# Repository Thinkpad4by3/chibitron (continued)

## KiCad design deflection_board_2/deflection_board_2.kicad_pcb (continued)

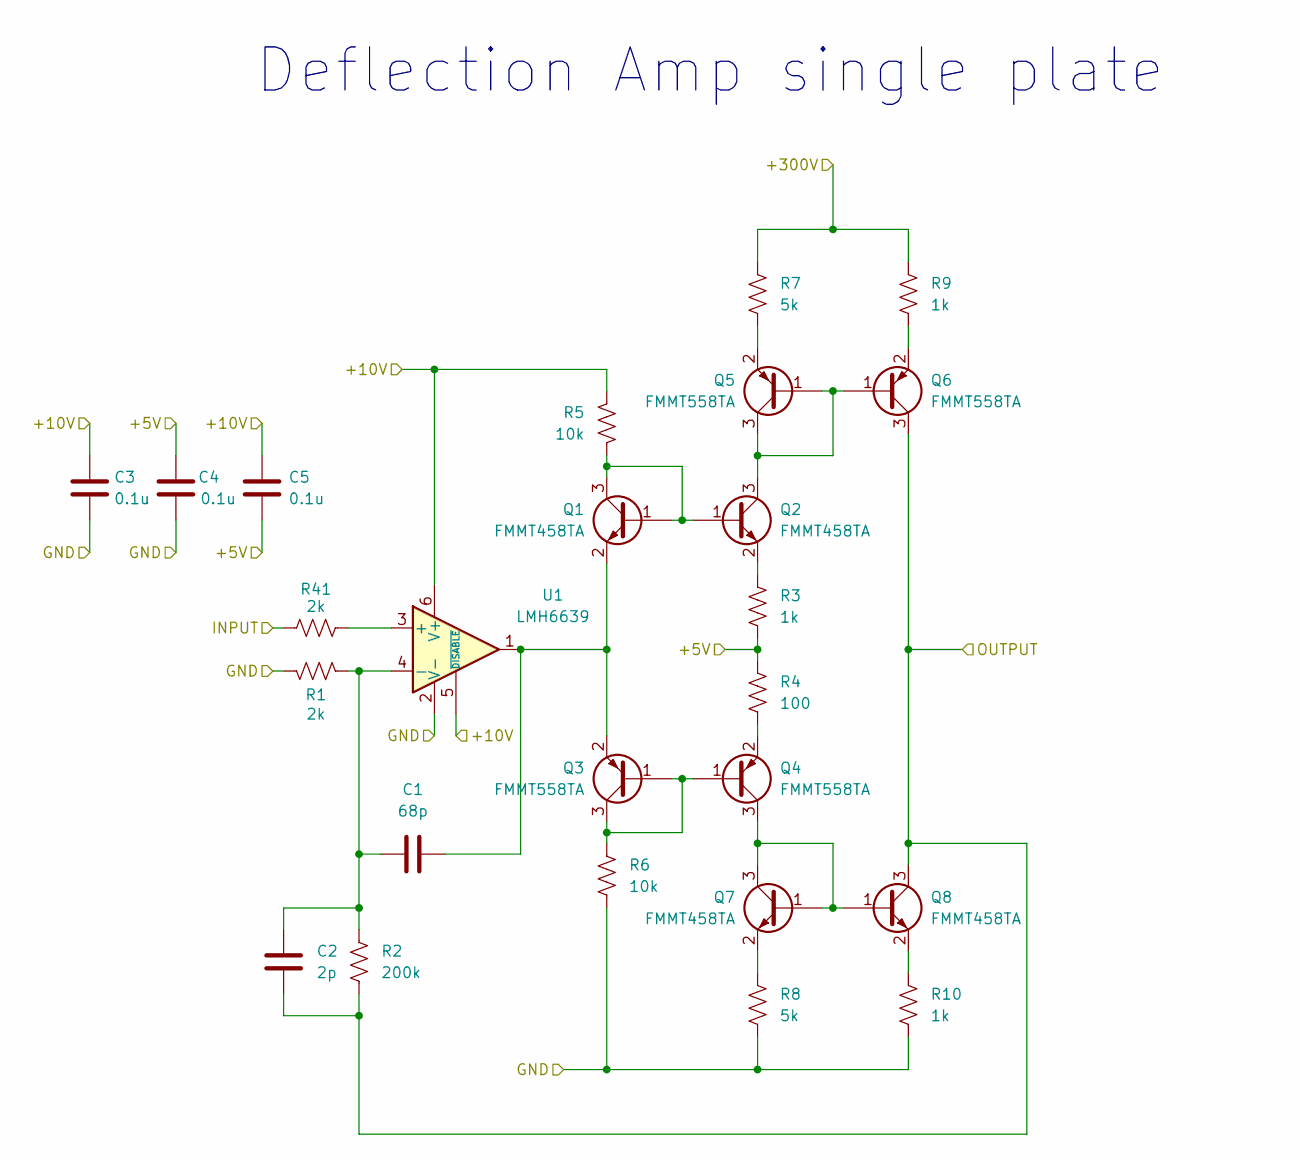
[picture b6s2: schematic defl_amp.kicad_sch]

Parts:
C1: 68p; C_0603_1608Metric_Pad1.08x0.95mm_HandSolder
C2: 2p; C_0603_1608Metric_Pad1.08x0.95mm_HandSolder
C3, C4, C5: 0.1u; C_0603_1608Metric_Pad1.08x0.95mm_HandSolder
Q1, Q2, Q7, Q8: FMMT458TA; SOT-23
Q3, Q4, Q5, Q6: FMMT558TA; SOT-23
R1, R41: 2k; R_1206_3216Metric_Pad1.30x1.75mm_HandSolder
R2: 200k; R_1206_3216Metric_Pad1.30x1.75mm_HandSolder
R3, R9, R10: 1k; R_1206_3216Metric_Pad1.30x1.75mm_HandSolder
R4: 100; R_1206_3216Metric_Pad1.30x1.75mm_HandSolder
R5, R6: 10k; R_0603_1608Metric_Pad0.98x0.95mm_HandSolder
R7, R8: 5k; R_1206_3216Metric_Pad1.30x1.75mm_HandSolder
U1: LMH6639; TSOT-23-6

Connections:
+5V: C4.1, C5.2, R3.2, R4.1; also elsewhere on the board
+10V: C3.1, C5.1, R5.1, U1.5 (~DISABLE), U1.6 (V+); also elsewhere on the board
+300V: R7.1, R9.1; also elsewhere on the board
/Deflection Amp X1/INPUT: R41.1; also elsewhere on the board
/Deflection Amp X1/OUTPUT: C2.1, Q6.3 (C), Q8.3 (C), R2.2; also elsewhere on the board
GND: C3.2, C4.2, R1.1, R6.2, R8.2, R10.2, U1.2 (V-); also elsewhere on the board
unnamed: Q1.1 (B), Q1.3 (C), Q2.1 (B), R5.2
unnamed: C1.2, Q1.2 (E), Q3.2 (E), U1.1
unnamed: Q2.3 (C), Q5.1 (B), Q5.3 (C), Q6.1 (B)
unnamed: Q2.2 (E), R3.1
unnamed: Q3.1 (B), Q3.3 (C), Q4.1 (B), R6.1
unnamed: Q4.3 (C), Q7.1 (B), Q7.3 (C), Q8.1 (B)
unnamed: Q4.2 (E), R4.2
unnamed: Q5.2 (E), R7.2
unnamed: Q6.2 (E), R9.2
unnamed: Q7.2 (E), R8.1
unnamed: Q8.2 (E), R10.1
unnamed: R41.2, U1.3 (+)
unnamed: C1.1, C2.2, R1.2, R2.1, U1.4 (-)

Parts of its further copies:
C6, C7, C8, C11, C12, C13, C16, C17, C18: 0.1u; C_0603_1608Metric_Pad1.08x0.95mm_HandSolder
C9, C14, C19: 2p; C_0603_1608Metric_Pad1.08x0.95mm_HandSolder
C10, C15, C20: 68p; C_0603_1608Metric_Pad1.08x0.95mm_HandSolder
Q9, Q11, Q14, Q16, Q17, Q19, Q22, Q24, Q25, Q27, Q30, Q32: FMMT458TA; SOT-23
Q10, Q12, Q13, Q15, Q18, Q20, Q21, Q23, Q26, Q28, Q29, Q31: FMMT558TA; SOT-23
R11, R21, R31, R42, R43, R44: 2k; R_1206_3216Metric_Pad1.30x1.75mm_HandSolder
R12, R22, R32: 200k; R_1206_3216Metric_Pad1.30x1.75mm_HandSolder
R13, R14, R23, R24, R33, R34: 10k; R_0603_1608Metric_Pad0.98x0.95mm_HandSolder
R15, R18, R25, R28, R35, R38: 5k; R_1206_3216Metric_Pad1.30x1.75mm_HandSolder
R16, R19, R20, R26, R29, R30, R36, R39, R40: 1k; R_1206_3216Metric_Pad1.30x1.75mm_HandSolder
R17, R27, R37: 100; R_1206_3216Metric_Pad1.30x1.75mm_HandSolder
U2, U3, U4: LMH6639; TSOT-23-6

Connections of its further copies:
+5V: C7.1, C8.2, C12.1, C13.2, C17.1, C18.2, R16.2, R17.1, R26.2, R27.1, R36.2, R37.1; also elsewhere on the board
+10V: C6.1, C8.1, C11.1, C13.1, C16.1, C18.1, R13.1, R23.1, R33.1, U2.5 (~DISABLE), U2.6 (V+), U3.5 (~DISABLE), U3.6 (V+), U4.5 (~DISABLE), U4.6 (V+); also elsewhere on the board
+300V: R15.1, R19.1, R25.1, R29.1, R35.1, R39.1; also elsewhere on the board
/Deflection Amp X2/INPUT: R42.1; also elsewhere on the board
/Deflection Amp X2/OUTPUT: C9.1, Q15.3 (C), Q16.3 (C), R12.2; also elsewhere on the board
/Deflection Amp Y1/INPUT: R43.1; also elsewhere on the board
/Deflection Amp Y1/OUTPUT: C14.1, Q23.3 (C), Q24.3 (C), R22.2; also elsewhere on the board
/Deflection Amp Y2/INPUT: R44.1; also elsewhere on the board
/Deflection Amp Y2/OUTPUT: C19.1, Q31.3 (C), Q32.3 (C), R32.2; also elsewhere on the board
GND: C6.2, C7.2, C11.2, C12.2, C16.2, C17.2, R11.1, R14.2, R18.2, R20.2, R21.1, R24.2, R28.2, R30.2, R31.1, R34.2, R38.2, R40.2, U2.2 (V-), U3.2 (V-), U4.2 (V-); also elsewhere on the board
unnamed: Q10.1 (B), Q10.3 (C), Q12.1 (B), R14.1
unnamed: C10.2, Q9.2 (E), Q10.2 (E), U2.1
unnamed: Q9.1 (B), Q9.3 (C), Q11.1 (B), R13.2
unnamed: Q11.3 (C), Q13.1 (B), Q13.3 (C), Q15.1 (B)
unnamed: Q11.2 (E), R16.1
unnamed: Q12.3 (C), Q14.1 (B), Q14.3 (C), Q16.1 (B)
unnamed: Q12.2 (E), R17.2
unnamed: Q13.2 (E), R15.2
unnamed: Q14.2 (E), R18.1
unnamed: Q15.2 (E), R19.2
unnamed: Q16.2 (E), R20.1
unnamed: Q17.1 (B), Q17.3 (C), Q19.1 (B), R23.2
unnamed: C15.2, Q17.2 (E), Q18.2 (E), U3.1
unnamed: Q18.1 (B), Q18.3 (C), Q20.1 (B), R24.1
unnamed: Q19.3 (C), Q21.1 (B), Q21.3 (C), Q23.1 (B)
unnamed: Q19.2 (E), R26.1
unnamed: Q20.3 (C), Q22.1 (B), Q22.3 (C), Q24.1 (B)
unnamed: Q20.2 (E), R27.2
unnamed: Q21.2 (E), R25.2
unnamed: Q22.2 (E), R28.1
unnamed: Q23.2 (E), R29.2
unnamed: Q24.2 (E), R30.1
unnamed: Q25.1 (B), Q25.3 (C), Q27.1 (B), R33.2
unnamed: C20.2, Q25.2 (E), Q26.2 (E), U4.1
unnamed: Q26.1 (B), Q26.3 (C), Q28.1 (B), R34.1
unnamed: Q27.3 (C), Q29.1 (B), Q29.3 (C), Q31.1 (B)
unnamed: Q27.2 (E), R36.1
unnamed: Q28.3 (C), Q30.1 (B), Q30.3 (C), Q32.1 (B)
unnamed: Q28.2 (E), R37.2
unnamed: Q29.2 (E), R35.2
unnamed: Q30.2 (E), R38.1
unnamed: Q31.2 (E), R39.2
unnamed: Q32.2 (E), R40.1
unnamed: R42.2, U2.3 (+)
unnamed: C9.2, C10.1, R11.2, R12.1, U2.4 (-)
unnamed: R43.2, U3.3 (+)
unnamed: C14.2, C15.1, R21.2, R22.1, U3.4 (-)
unnamed: R44.2, U4.3 (+)
unnamed: C19.2, C20.1, R31.2, R32.1, U4.4 (-)

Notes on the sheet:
Deflection Amp single plate

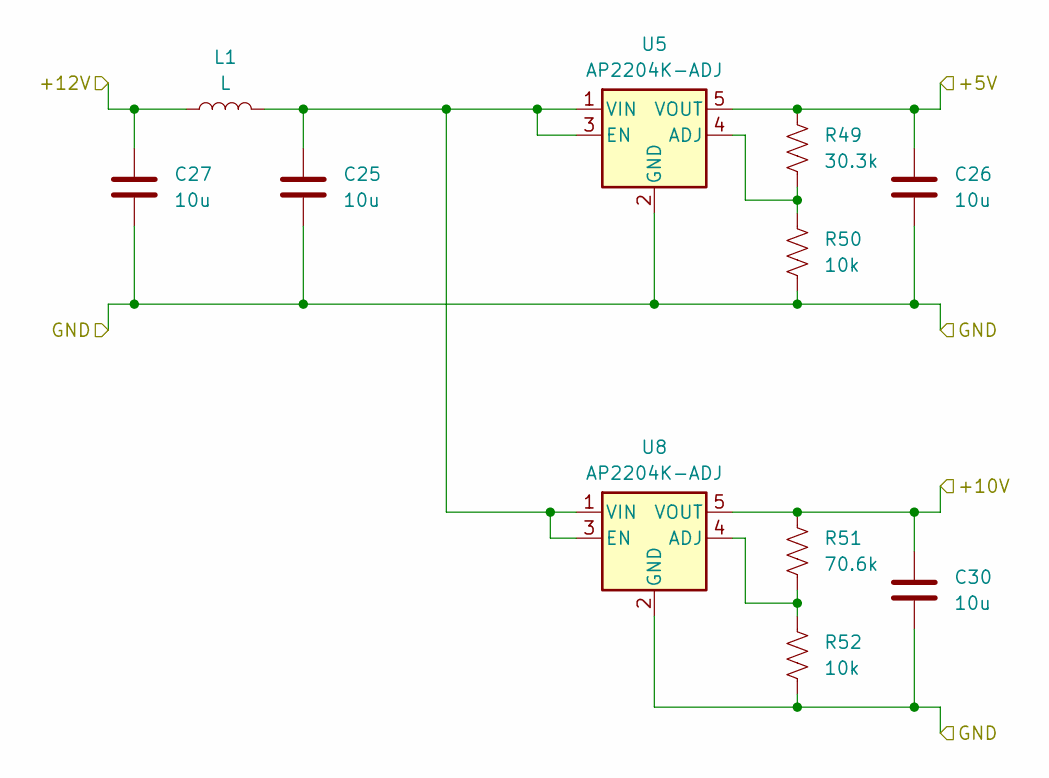
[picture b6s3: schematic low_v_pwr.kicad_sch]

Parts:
C25, C26, C27, C30: 10u; C_0603_1608Metric
L1: L; L_APV_ANR4018
R49: 30.3k; R_0805_2012Metric
R50, R52: 10k; R_0805_2012Metric
R51: 70.6k; R_0805_2012Metric
U5, U8: AP2204K-ADJ; SOT-23-5

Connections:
+5V: C26.1, R49.1, U5.5 (VOUT); also elsewhere on the board
+10V: C30.1, R51.1, U8.5 (VOUT); also elsewhere on the board
+12V: C27.1, L1.1; also elsewhere on the board
GND: C25.2, C26.2, C27.2, C30.2, R50.2, R52.2, U5.2 (GND), U8.2 (GND); also elsewhere on the board
unnamed: R49.2, R50.1, U5.4 (ADJ)
unnamed: C25.1, L1.2, U5.1 (VIN), U5.3 (EN), U8.1 (VIN), U8.3 (EN)
unnamed: R51.2, R52.1, U8.4 (ADJ)

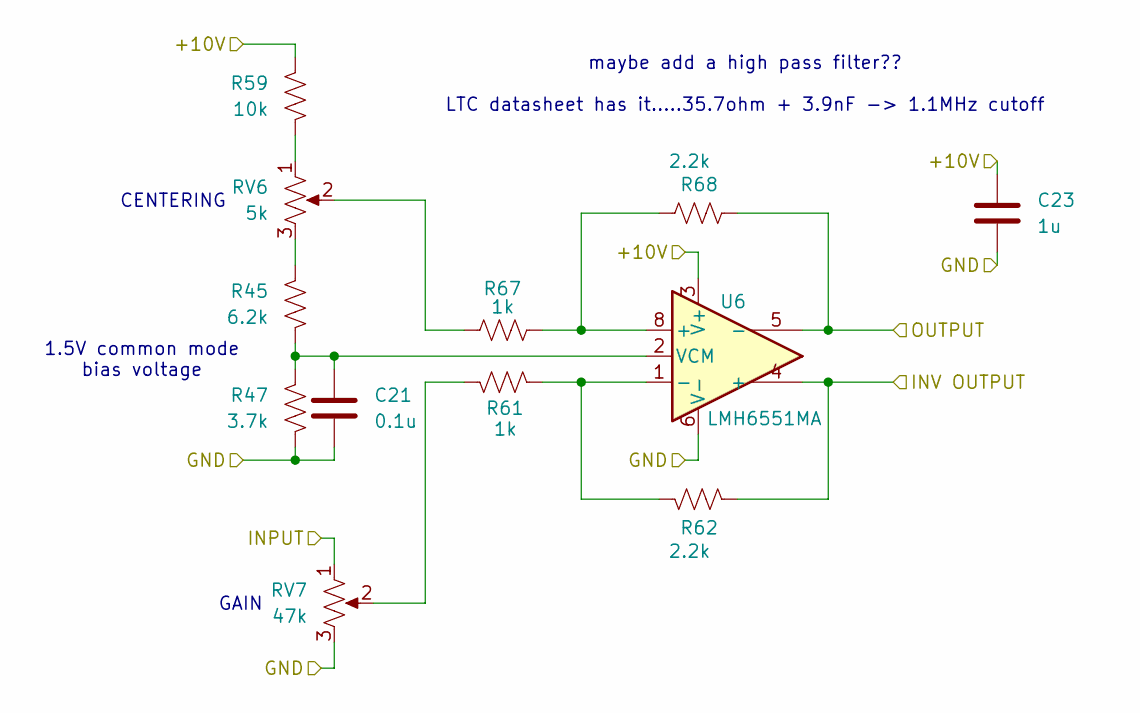
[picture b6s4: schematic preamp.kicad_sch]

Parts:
C21: 0.1u; C_0603_1608Metric
C23: 1u; C_0603_1608Metric
R45: 6.2k; R_0603_1608Metric
R47: 3.7k; R_0603_1608Metric
R59: 10k; R_0603_1608Metric_Pad0.98x0.95mm_HandSolder
R61, R67: 1k; R_0603_1608Metric_Pad0.98x0.95mm_HandSolder
R62, R68: 2.2k; R_0603_1608Metric_Pad0.98x0.95mm_HandSolder
RV6: 5k; Potentiometer_Bourns_3296W_Vertical
RV7: 47k; Potentiometer_Bourns_3296W_Vertical
U6: LMH6551MA; SOIC-8_3.9x4.9mm_P1.27mm

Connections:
+10V: C23.1, R59.1, U6.3 (V+); also elsewhere on the board
/X Pre-amp/INPUT: RV7.1; also elsewhere on the board
/X Pre-amp/INV OUTPUT: R62.2, U6.4 (+); also elsewhere on the board
/X Pre-amp/OUTPUT: R68.2, U6.5 (-); also elsewhere on the board
GND: C21.2, C23.2, R47.2, RV7.3, U6.6 (V-); also elsewhere on the board
unnamed: R45.1, RV6.3
unnamed: R59.2, RV6.1
unnamed: R61.1, R62.1, U6.1 (-)
unnamed: R61.2, RV7.2
unnamed: R67.1, R68.1, U6.8 (+)
unnamed: R67.2, RV6.2
unnamed: C21.1, R45.2, R47.1, U6.2 (VCM)

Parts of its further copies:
C22: 0.1u; C_0603_1608Metric
C24: 1u; C_0603_1608Metric
R63: 10k; R_0603_1608Metric_Pad0.98x0.95mm_HandSolder
R65, R69: 1k; R_0603_1608Metric_Pad0.98x0.95mm_HandSolder
R66, R70: 2.2k; R_0603_1608Metric_Pad0.98x0.95mm_HandSolder
RV8: 5k; Potentiometer_Bourns_3296W_Vertical
RV9: 47k; Potentiometer_Bourns_3296W_Vertical
U7: LMH6551MA; SOIC-8_3.9x4.9mm_P1.27mm

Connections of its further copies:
+10V: C24.1, R63.1, U7.3 (V+); also elsewhere on the board
/Y Pre-amp/INPUT: RV9.1; also elsewhere on the board
/Y Pre-amp/INV OUTPUT: R66.2, U7.4 (+); also elsewhere on the board
/Y Pre-amp/OUTPUT: R70.2, U7.5 (-); also elsewhere on the board
GND: C22.2, C24.2, RV9.3, U7.6 (V-); also elsewhere on the board
unnamed 64: RV8.3; also elsewhere on the board
unnamed: R63.2, RV8.1
unnamed: R65.1, R66.1, U7.1 (-)
unnamed: R65.2, RV9.2
unnamed: R69.1, R70.1, U7.8 (+)
unnamed: R69.2, RV8.2
unnamed 86: C22.1, U7.2 (VCM); also elsewhere on the board

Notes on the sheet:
CENTERING
maybe add a high pass filter?? LTC datasheet has it.....35.7ohm + 3.9nF -> 1.1MHz cutoff
GAIN
1.5V common mode bias voltage

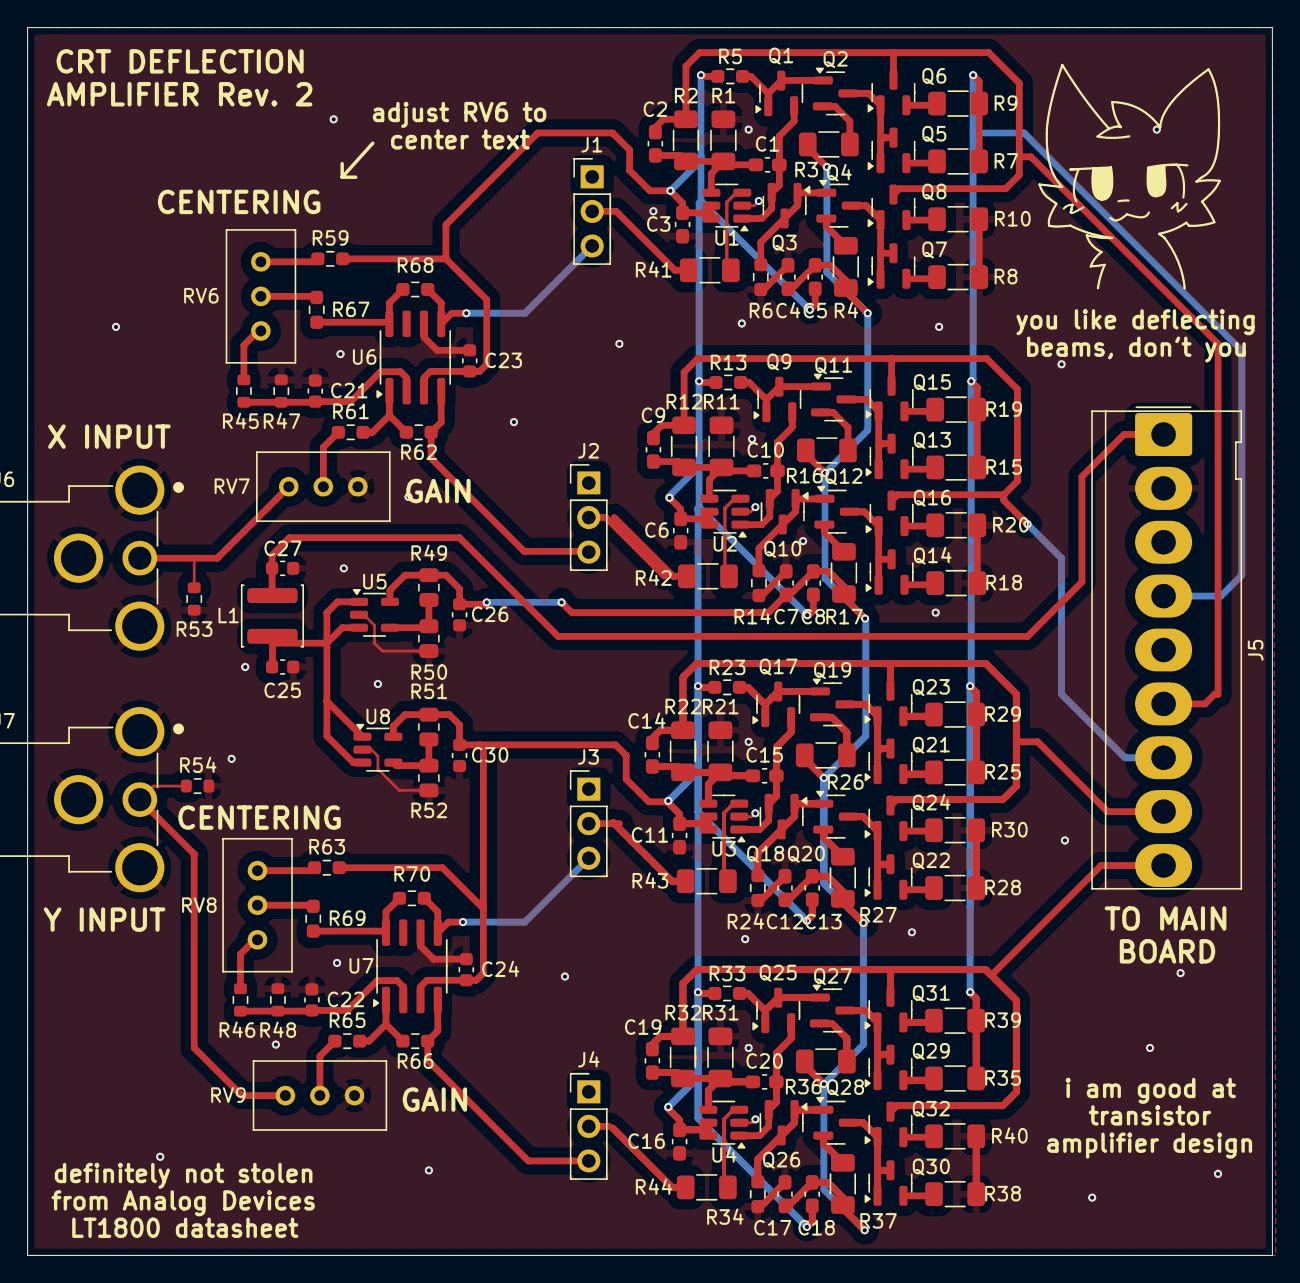
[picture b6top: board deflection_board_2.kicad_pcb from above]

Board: 2 copper layers, 91.5 x 90.2 mm, 144 parts (0 on the bottom side), 88 nets.

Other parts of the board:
R46: 6.25k; R_0603_1608Metric
R48: 3.75k; R_0603_1608Metric

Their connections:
GND: R48.2; also elsewhere on the board
unnamed 64: R46.1; also elsewhere on the board
unnamed 86: R46.2, R48.1; also elsewhere on the board

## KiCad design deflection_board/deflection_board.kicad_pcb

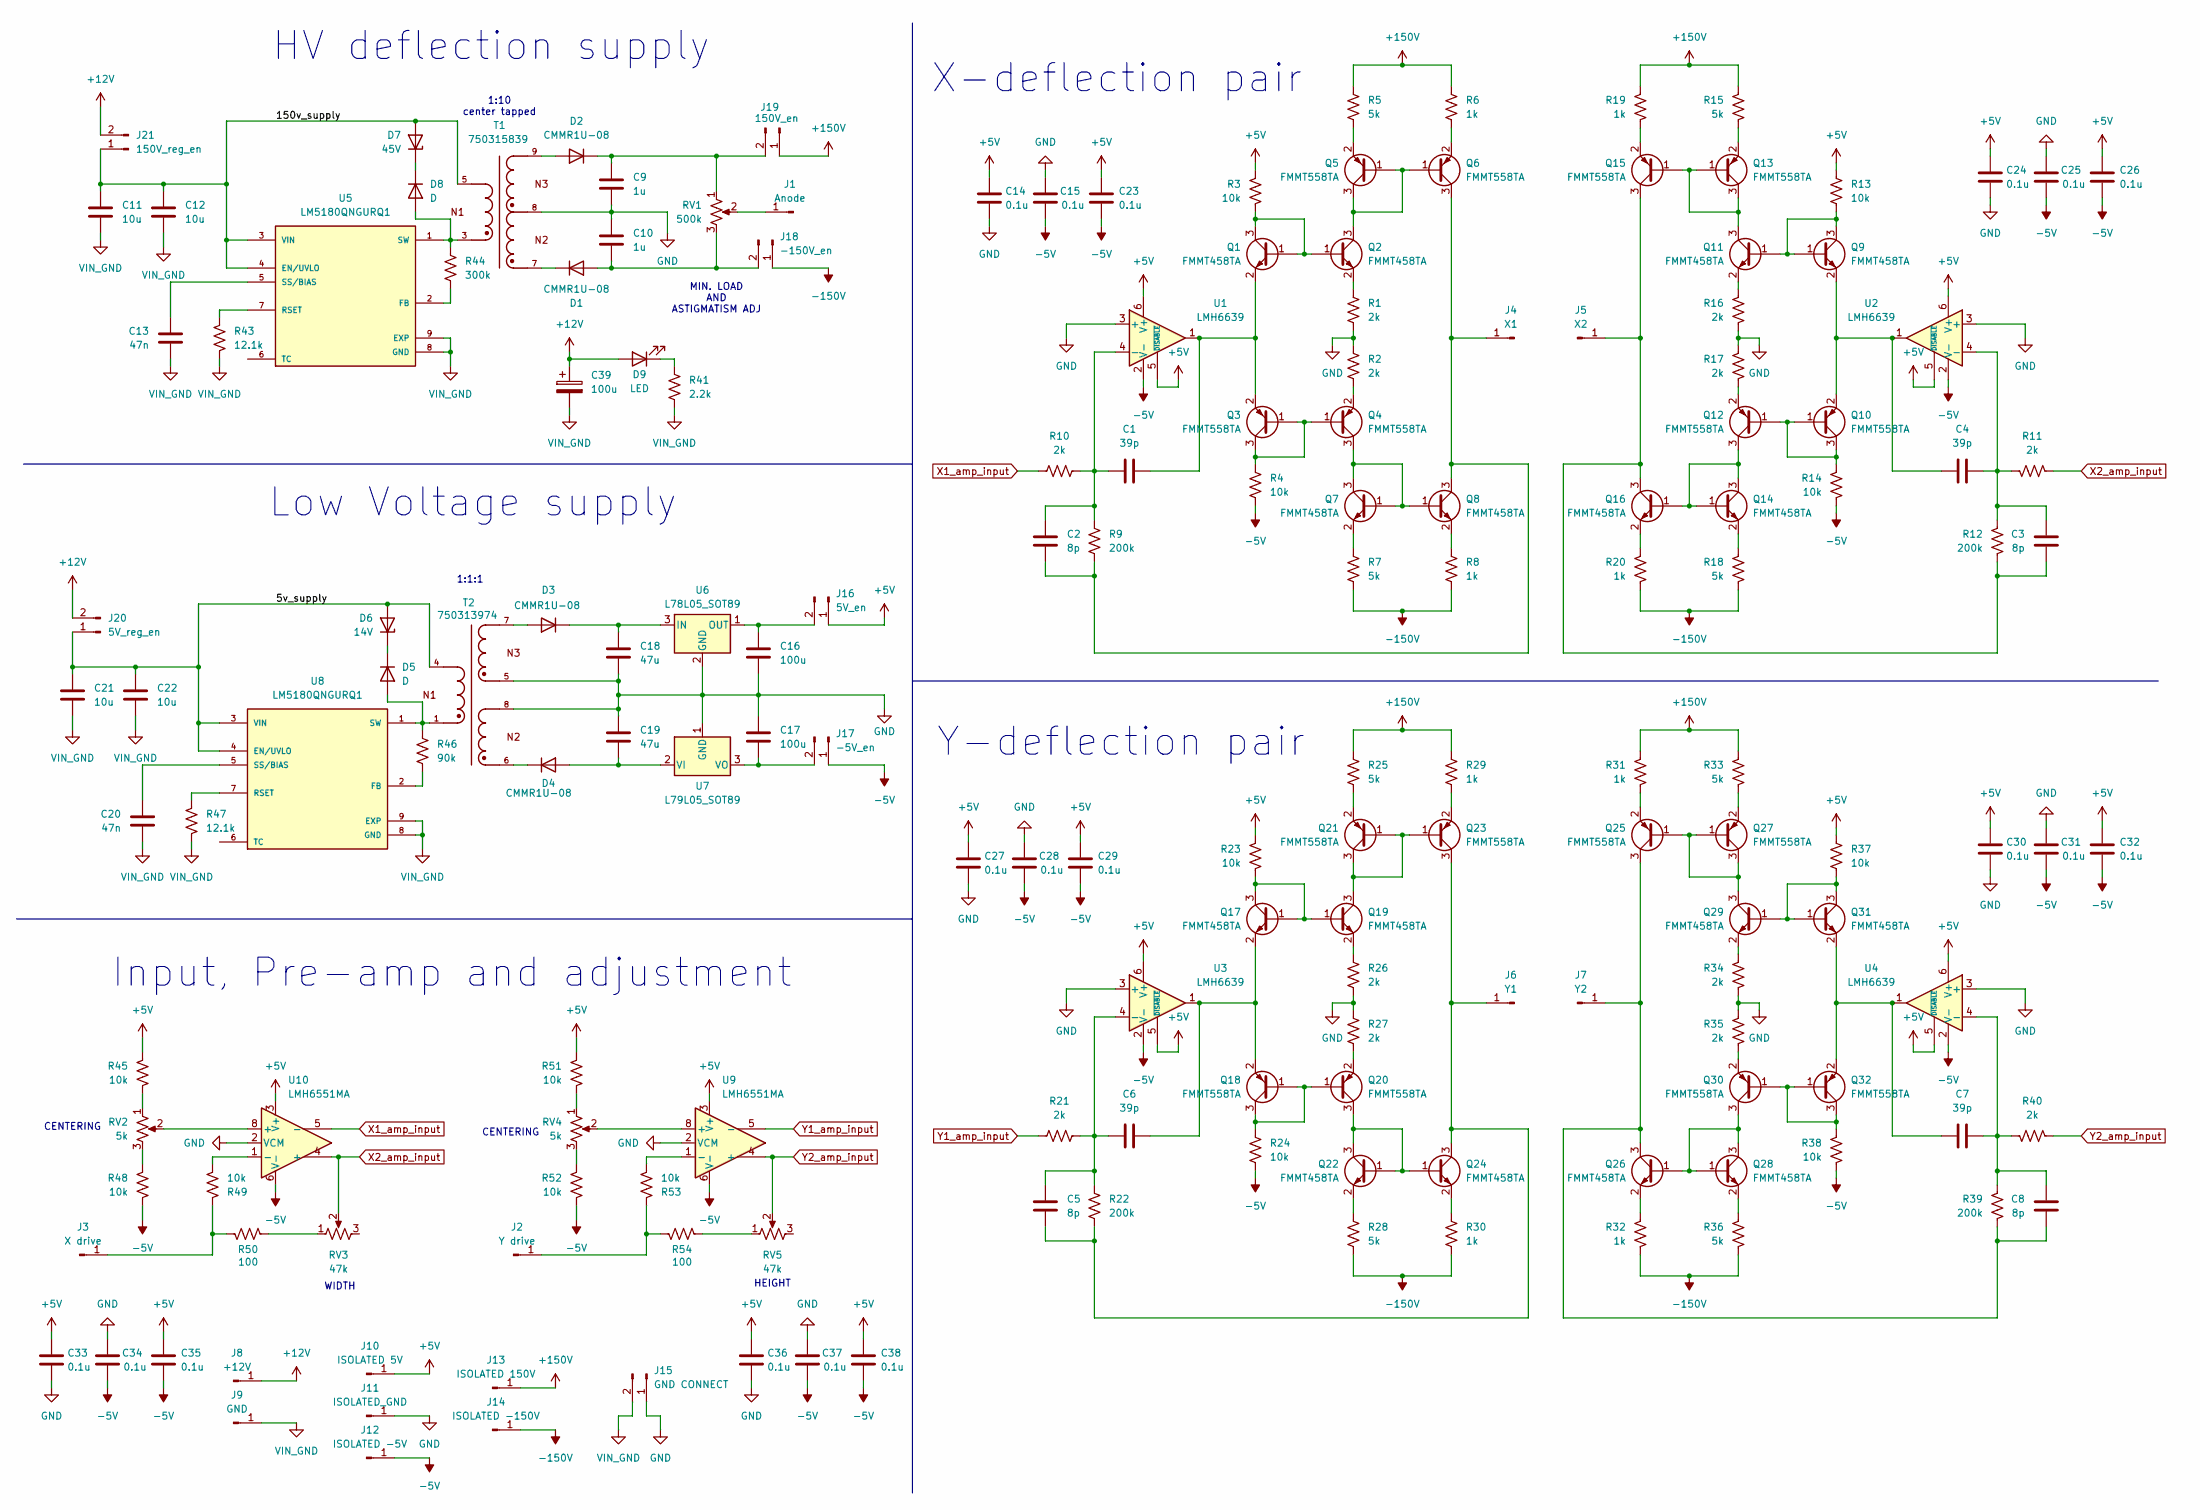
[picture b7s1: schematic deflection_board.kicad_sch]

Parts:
C1, C4, C6, C7: 39p; C_0603_1608Metric_Pad1.08x0.95mm_HandSolder
C2, C3, C5, C8: 8p; C_0603_1608Metric_Pad1.08x0.95mm_HandSolder
C9, C10: 1u; C_1812_4532Metric_Pad1.57x3.40mm_HandSolder
C11, C12, C21, C22: 10u; C_0805_2012Metric_Pad1.18x1.45mm_HandSolder
C13, C20: 47n; C_0603_1608Metric_Pad1.08x0.95mm_HandSolder
C14, C15, C23, C24, C25, C26, C27, C28, C29, C30, C31, C32, C33, C34, C35, C36, C37, C38: 0.1u; C_0603_1608Metric_Pad1.08x0.95mm_HandSolder
C16, C17: 100u; C_1206_3216Metric_Pad1.33x1.80mm_HandSolder
C18, C19: 47u; C_1210_3225Metric_Pad1.33x2.70mm_HandSolder
C39: 100u; C_Elec_6.3x7.7
D1, D2, D3, D4: CMMR1U-08; D_SOD-123F
D5, D8: D; D_SOD-123
D6: 14V; D_SOD-123
D7: 45V; D_SOD-123
D9: LED; LED_0805_2012Metric
J1: Anode; PinHeader_1x01_P2.54mm_Vertical
J2: Y drive; PinHeader_1x01_P2.54mm_Vertical
J3: X drive; PinHeader_1x01_P2.54mm_Vertical
J4: X1; PinHeader_1x01_P2.54mm_Vertical
J5: X2; PinHeader_1x01_P2.54mm_Vertical
J6: Y1; PinHeader_1x01_P2.54mm_Vertical
J7: Y2; PinHeader_1x01_P2.54mm_Vertical
J8: +12V; PinHeader_1x01_P2.54mm_Vertical
J9: GND; PinHeader_1x01_P2.54mm_Vertical
J10: ISOLATED 5V; PinHeader_1x01_P2.54mm_Vertical
J11: ISOLATED_GND; PinHeader_1x01_P2.54mm_Vertical
J12: ISOLATED -5V; PinHeader_1x01_P2.54mm_Vertical
J13: ISOLATED 150V; PinHeader_1x01_P2.54mm_Vertical
J14: ISOLATED -150V; PinHeader_1x01_P2.54mm_Vertical
J15: GND CONNECT; PinHeader_1x02_P2.54mm_Vertical
J16: 5V_en; PinHeader_1x02_P2.54mm_Vertical
J17: -5V_en; PinHeader_1x02_P2.54mm_Vertical
J18: -150V_en; PinHeader_1x02_P2.54mm_Vertical
J19: 150V_en; PinHeader_1x02_P2.54mm_Vertical
J20: 5V_reg_en; PinHeader_1x02_P2.54mm_Vertical
J21: 150V_reg_en; PinHeader_1x02_P2.54mm_Vertical
Q1, Q2, Q7, Q8, Q9, Q11, Q14, Q16, Q17, Q19, Q22, Q24, Q26, Q28, Q29, Q31: FMMT458TA; SOT-23
Q3, Q4, Q5, Q6, Q10, Q12, Q13, Q15, Q18, Q20, Q21, Q23, Q25, Q27, Q30, Q32: FMMT558TA; SOT-23
R1, R2, R10, R11, R16, R17, R21, R26, R27, R34, R35, R40: 2k; R_1206_3216Metric_Pad1.30x1.75mm_HandSolder
R3, R4, R13, R14, R23, R24, R37, R38, R45, R48, R49, R51, R52, R53: 10k; R_0603_1608Metric_Pad0.98x0.95mm_HandSolder
R5, R7, R15, R18, R25, R28, R33, R36: 5k; R_1206_3216Metric_Pad1.30x1.75mm_HandSolder
R6, R8, R19, R20, R29, R30, R31, R32: 1k; R_1206_3216Metric_Pad1.30x1.75mm_HandSolder
R9, R12, R22, R39: 200k; R_1206_3216Metric_Pad1.30x1.75mm_HandSolder
R41: 2.2k; R_0805_2012Metric_Pad1.20x1.40mm_HandSolder
R43, R47: 12.1k; R_0603_1608Metric_Pad0.98x0.95mm_HandSolder
R44: 300k; R_0603_1608Metric_Pad0.98x0.95mm_HandSolder
R46: 90k; R_0603_1608Metric_Pad0.98x0.95mm_HandSolder
R50, R54: 100; R_0603_1608Metric_Pad0.98x0.95mm_HandSolder
RV1: 500k; Potentiometer_Bourns_3296W_Vertical
RV2, RV4: 5k; Potentiometer_Bourns_3296W_Vertical
RV3, RV5: 47k; Potentiometer_Bourns_3296W_Vertical
T1: 750315839; WE-FLYLT_EP13_5465; PART-NUMBER 750315839
T2: 750313974; WE-FLYLT_EP10_6052; PART-NUMBER 750313974
U1, U2, U3, U4: LMH6639; TSOT-23-6
U5, U8: LM5180QNGURQ1; SON80P400X400X80-9N; PARTREV A
U6: L78L05_SOT89; SOT-89-3
U7: L79L05_SOT89; SOT-89-3
U9, U10: LMH6551MA; SOIC-8_3.9x4.9mm_P1.27mm

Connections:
+5V: C14.1, C23.1, C24.1, C26.1, C27.1, C29.1, C30.1, C32.1, C33.1, C35.1, C36.1, C38.1, J10.1, J16.1, R3.1, R13.1, R23.1, R37.1, R45.1, R51.1, U1.5 (~DISABLE), U1.6 (V+), U2.5 (~DISABLE), U2.6 (V+), U3.5 (~DISABLE), U3.6 (V+), U4.5 (~DISABLE), U4.6 (V+), U9.3 (V+), U10.3 (V+)
+12V: C39.1, D9.2 (A), J8.1, J20.2, J21.2
+150V: J13.1, J19.1, R5.1, R6.1, R15.1, R19.1, R25.1, R29.1, R31.1, R33.1
-5V: C15.2, C23.2, C25.2, C26.2, C28.2, C29.2, C31.2, C32.2, C34.2, C35.2, C37.2, C38.2, J12.1, J17.1, R4.2, R14.2, R24.2, R38.2, R48.2, R52.2, U1.2 (V-), U2.2 (V-), U3.2 (V-), U4.2 (V-), U9.6 (V-), U10.6 (V-)
-150V: J14.1, J18.1, R7.2, R8.2, R18.2, R20.2, R28.2, R30.2, R32.2, R36.2
/5v_supply: C21.1, C22.1, D6.2 (A), J20.1, T2.4, U8.3 (VIN), U8.4 (EN/UVLO)
/150v_supply: C11.1, C12.1, D7.2 (A), J21.1, T1.5, U5.3 (VIN), U5.4 (EN/UVLO)
GND: C9.2, C10.1, C14.2, C15.1, C16.2, C17.1, C18.2, C19.1, C24.2, C25.1, C27.2, C28.1, C30.2, C31.1, C33.2, C34.1, C36.2, C37.1, J11.1, J15.1, R1.2, R2.1, R16.2, R17.1, R26.2, R27.1, R34.2, R35.1, T1.8, T2.5, T2.8, U1.3 (+), U2.3 (+), U3.3 (+), U4.3 (+), U6.2 (GND), U7.1 (GND), U9.2 (VCM), U10.2 (VCM)
unnamed: C10.2, D1.2 (A), J18.2, RV1.3
unnamed: D1.1 (K), T1.7
unnamed: D2.2 (A), T1.9
unnamed: C9.1, D2.1 (K), J19.2, RV1.1
unnamed: D3.2 (A), T2.7
unnamed: C18.1, D3.1 (K), U6.3 (IN)
unnamed: C19.2, D4.2 (A), U7.2 (VI)
unnamed: D4.1 (K), T2.6
unnamed: D5.2 (A), R46.1, T2.1, U8.1 (SW)
unnamed: D5.1 (K), D6.1 (K)
unnamed: D7.1 (K), D8.1 (K)
unnamed: D8.2 (A), R44.1, T1.3, U5.1 (SW)
unnamed: D9.1 (K), R41.2
unnamed: J1.1, RV1.2
unnamed: J2.1, R53.1, R54.1
unnamed: J3.1, R49.1, R50.1
unnamed: C2.1, J4.1, Q6.3 (C), Q8.3 (C), R9.2
unnamed: C3.1, J5.1, Q15.3 (C), Q16.3 (C), R12.2
unnamed: C5.1, J6.1, Q23.3 (C), Q24.3 (C), R22.2
unnamed: C8.1, J7.1, Q25.3 (C), Q26.3 (C), R39.2
unnamed: C16.1, J16.2, U6.1 (OUT)
unnamed: C17.2, J17.2, U7.3 (VO)
unnamed: Q1.1 (B), Q1.3 (C), Q2.1 (B), R3.2
unnamed: C1.2, Q1.2 (E), Q3.2 (E), U1.1
unnamed: Q2.3 (C), Q5.1 (B), Q5.3 (C), Q6.1 (B)
unnamed: Q2.2 (E), R1.1
unnamed: Q3.1 (B), Q3.3 (C), Q4.1 (B), R4.1
unnamed: Q4.3 (C), Q7.1 (B), Q7.3 (C), Q8.1 (B)
unnamed: Q4.2 (E), R2.2
unnamed: Q5.2 (E), R5.2
unnamed: Q6.2 (E), R6.2
unnamed: Q7.2 (E), R7.1
unnamed: Q8.2 (E), R8.1
unnamed: Q10.1 (B), Q10.3 (C), Q12.1 (B), R14.1
unnamed: C4.2, Q9.2 (E), Q10.2 (E), U2.1
unnamed: Q9.1 (B), Q9.3 (C), Q11.1 (B), R13.2
unnamed: Q11.3 (C), Q13.1 (B), Q13.3 (C), Q15.1 (B)
unnamed: Q11.2 (E), R16.1
unnamed: Q12.3 (C), Q14.1 (B), Q14.3 (C), Q16.1 (B)
unnamed: Q12.2 (E), R17.2
unnamed: Q13.2 (E), R15.2
unnamed: Q14.2 (E), R18.1
unnamed: Q15.2 (E), R19.2
unnamed: Q16.2 (E), R20.1
unnamed: Q17.1 (B), Q17.3 (C), Q19.1 (B), R23.2
unnamed: C6.2, Q17.2 (E), Q18.2 (E), U3.1
unnamed: Q18.1 (B), Q18.3 (C), Q20.1 (B), R24.1
unnamed: Q19.3 (C), Q21.1 (B), Q21.3 (C), Q23.1 (B)
unnamed: Q19.2 (E), R26.1
unnamed: Q20.3 (C), Q22.1 (B), Q22.3 (C), Q24.1 (B)
unnamed: Q20.2 (E), R27.2
unnamed: Q21.2 (E), R25.2
unnamed: Q22.2 (E), R28.1
unnamed: Q23.2 (E), R29.2
unnamed: Q24.2 (E), R30.1
unnamed: Q25.1 (B), Q27.1 (B), Q27.3 (C), Q29.3 (C)
unnamed: Q25.2 (E), R31.2
unnamed: Q26.1 (B), Q28.1 (B), Q28.3 (C), Q30.3 (C)
unnamed: Q26.2 (E), R32.1
unnamed: Q27.2 (E), R33.2
unnamed: Q28.2 (E), R36.1
unnamed: Q29.1 (B), Q31.1 (B), Q31.3 (C), R37.2
unnamed: Q29.2 (E), R34.1
unnamed: Q30.1 (B), Q32.1 (B), Q32.3 (C), R38.1
unnamed: Q30.2 (E), R35.2
unnamed: C7.2, Q31.2 (E), Q32.2 (E), U4.1
unnamed: R45.2, RV2.1
unnamed: R48.1, RV2.3
unnamed: R49.2, U10.1 (-)
unnamed: R50.2, RV3.1
unnamed: R51.2, RV4.1
unnamed: R52.1, RV4.3
unnamed: R53.2, U9.1 (-)
unnamed: R54.2, RV5.1
unnamed: RV2.2, U10.8 (+)
unnamed: RV4.2, U9.8 (+)
unnamed: C1.1, C2.2, R9.1, R10.2, U1.4 (-)
unnamed: C3.2, C4.1, R11.2, R12.1, U2.4 (-)
unnamed: C5.2, C6.1, R21.2, R22.1, U3.4 (-)
unnamed: C7.1, C8.2, R39.1, R40.2, U4.4 (-)
unnamed: R44.2, U5.2 (FB)
unnamed: R43.1, U5.7 (RSET)
unnamed: C13.1, U5.5 (SS/BIAS)
unnamed: R46.2, U8.2 (FB)
unnamed: R47.1, U8.7 (RSET)
unnamed: C20.1, U8.5 (SS/BIAS)
VIN_GND: C11.2, C12.2, C13.2, C20.2, C21.2, C22.2, C39.2, J9.1, J15.2, R41.1, R43.2, R47.2, U5.8 (GND), U5.9 (EXP), U8.8 (GND), U8.9 (EXP)
X1_amp_input: R10.1, U10.5 (-)
X2_amp_input: R11.1, RV3.2, U10.4 (+)
Y1_amp_input: R21.1, U9.5 (-)
Y2_amp_input: R40.1, RV5.2, U9.4 (+)

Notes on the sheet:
Low Voltage supply
MIN. LOAD AND ASTIGMATISM ADJ
Input, Pre-amp and adjustment
Y-deflection pair
HV deflection supply
X-deflection pair
CENTERING
1:10 center tapped
HEIGHT
WIDTH
1:1:1

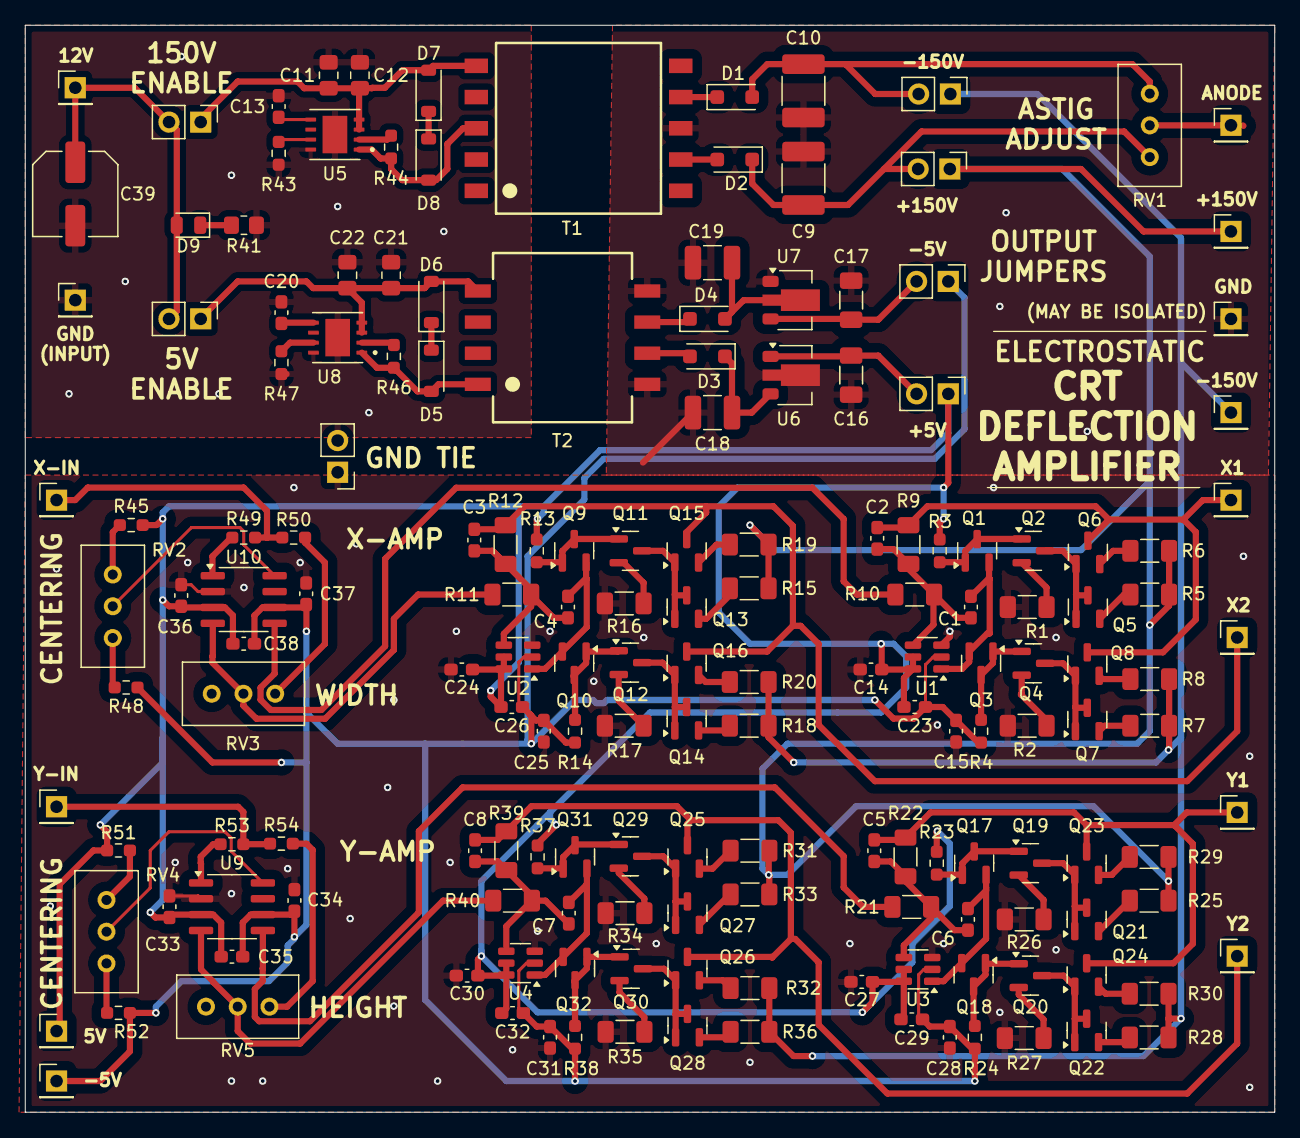
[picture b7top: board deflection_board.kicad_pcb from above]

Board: 2 copper layers, 100.0 x 87.0 mm, 171 parts (0 on the bottom side), 99 nets.
